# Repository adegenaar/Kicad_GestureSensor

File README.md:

# Kicad_GestureSensor
Small module utilizing the APDS-9990 for gesture sensing

The auto-generation of the KiCad exports was cribbed from:
* [nerdyscout](https://github.com/nerdyscout/kicad-exports)
* [INTI - CMNB](https://github.com/INTI-CMNB/KiBot)

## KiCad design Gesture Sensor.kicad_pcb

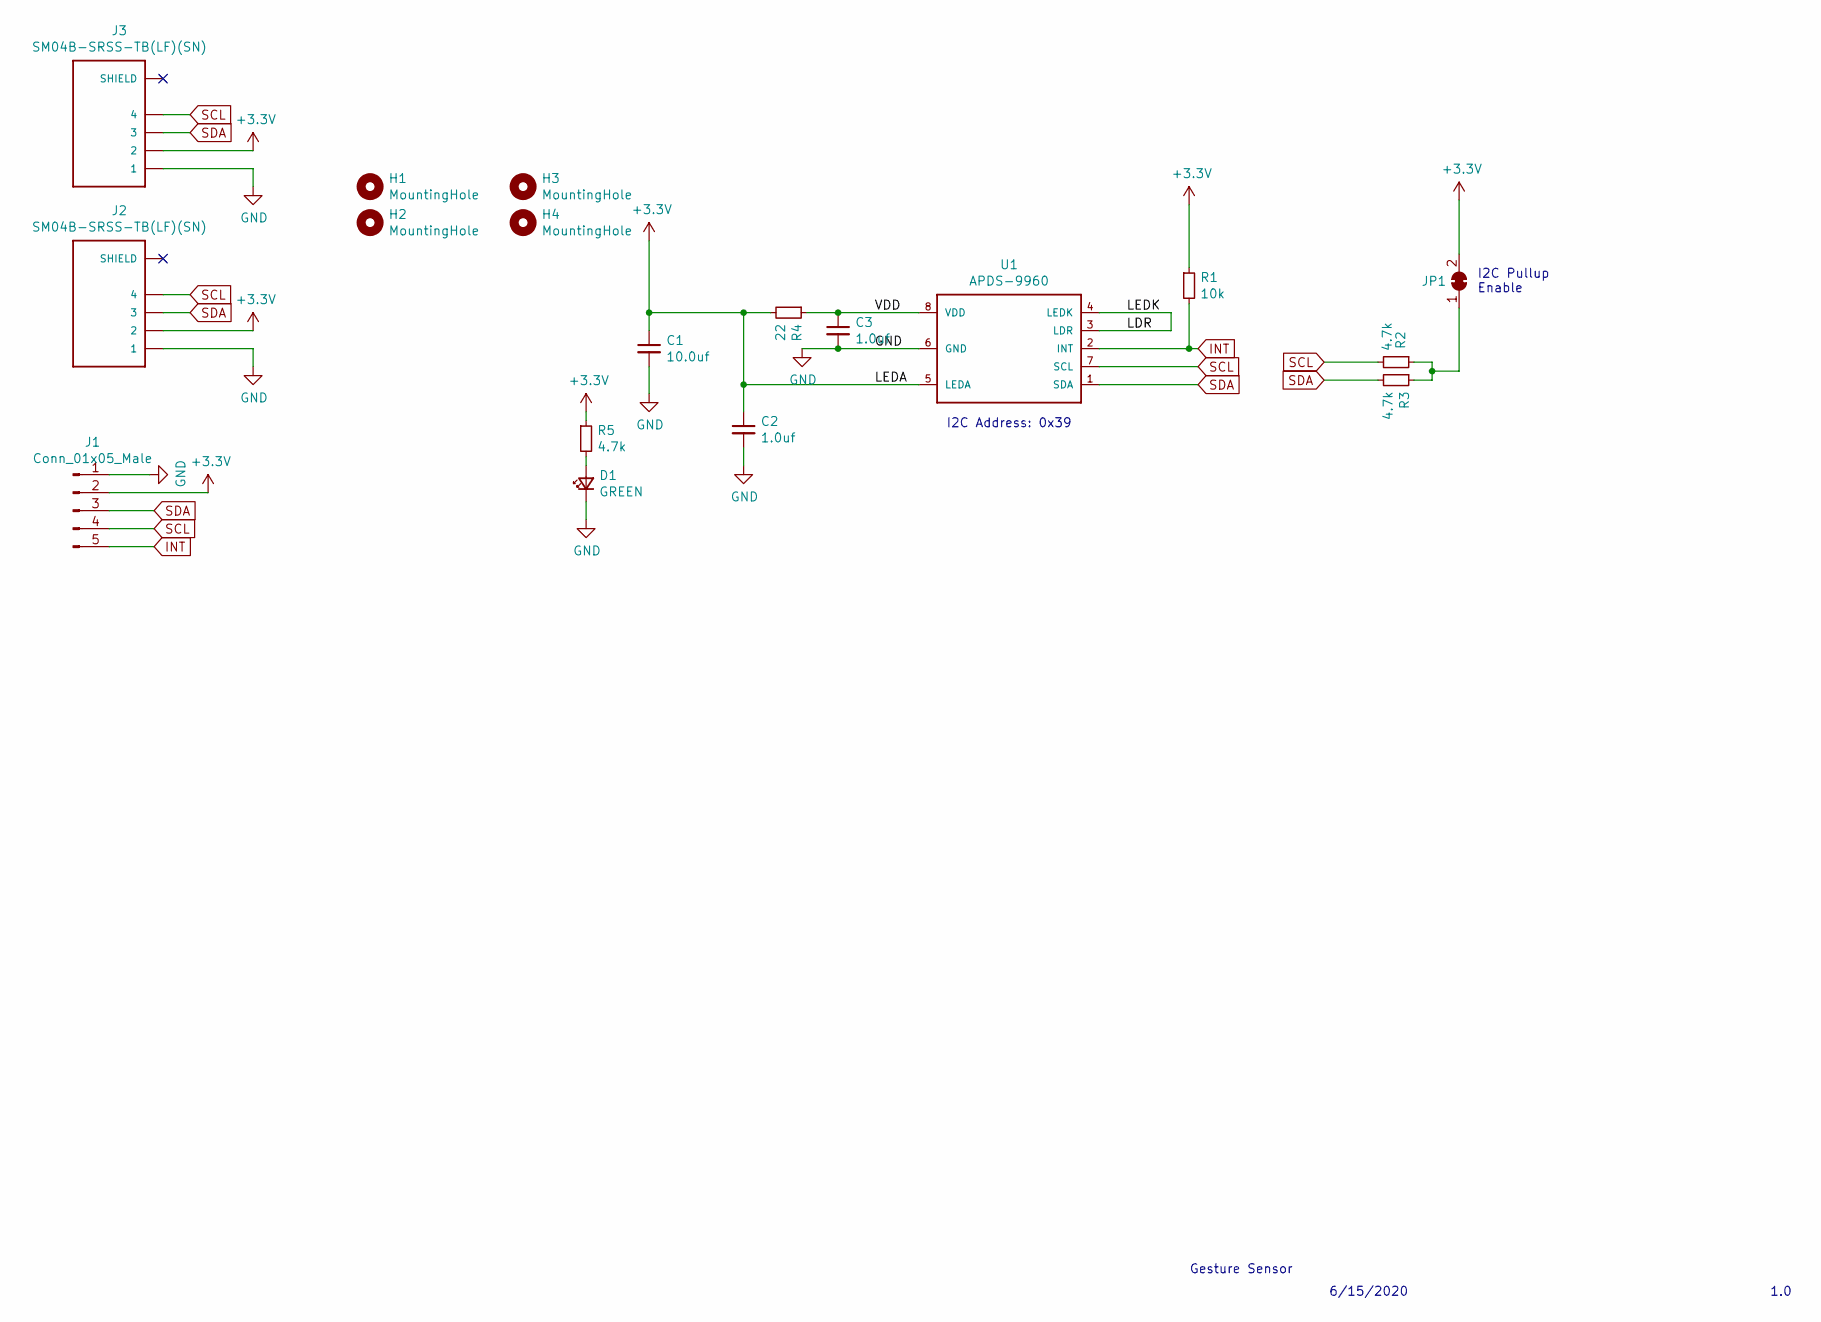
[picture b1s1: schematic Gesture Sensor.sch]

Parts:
C1: 10.0uf; C_0805_2012Metric_Pad1.15x1.40mm_HandSolder
C2, C3: 1.0uf; C_0805_2012Metric_Pad1.15x1.40mm_HandSolder
D1: GREEN; LED_0805_2012Metric
H1, H2, H3, H4: MountingHole; MountingHole_2.2mm_M2_ISO14580_Pad
J1: Conn_01x05_Male; PinHeader_1x05_P2.54mm_Vertical
J2, J3: SM04B-SRSS-TB(LF)(SN); JST_SM04B-SRSS-TB(LF)(SN)
JP1: SolderJumper_2_Bridged; SolderJumper-2_P1.3mm_Bridged_RoundedPad1.0x1.5mm
R1: 10k; R_0805_2012Metric_Pad1.15x1.40mm_HandSolder
R2, R3, R5: 4.7k; R_0805_2012Metric_Pad1.15x1.40mm_HandSolder
R4: 22; R_0805_2012Metric_Pad1.15x1.40mm_HandSolder
U1: APDS-9960

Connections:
+3V3: C1.1, C2.1, J1.2, J2.2, J3.2, JP1.2 (B), R1.1, R4.2, R5.1, U1.5 (LEDA)
/LDR: U1.3 (LDR), U1.4 (LEDK)
/VDD: C3.1, R4.1, U1.8 (VDD)
GND: C1.2, C2.2, C3.2, D1.1 (K), J1.1, J2.1, J3.1, U1.6 (GND)
INT: J1.5, R1.2, U1.2 (INT)
unnamed: D1.2 (A), R5.2
unnamed: J2.S1 (SHIELD), J2.S2 (SHIELD)
unnamed: J3.S1 (SHIELD), J3.S2 (SHIELD)
unnamed: JP1.1 (A), R2.1, R3.1
SCL: J1.4, J2.4, J3.4, R2.2, U1.7 (SCL)
SDA: J1.3, J2.3, J3.3, R3.2, U1.1 (SDA)

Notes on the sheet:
I2C Address: 0x39
I2C Pullup Enable
Gesture Sensor
6/15/2020
1.0

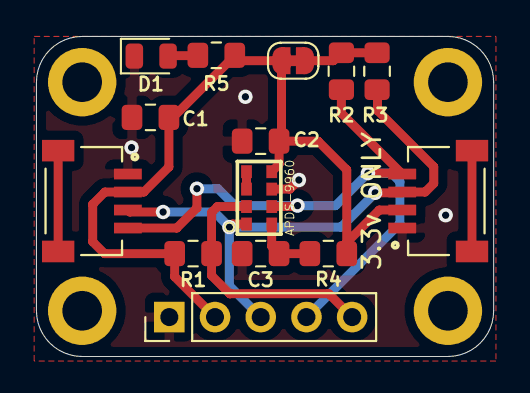
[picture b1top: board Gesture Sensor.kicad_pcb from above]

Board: 2 copper layers, 25.4 x 17.8 mm, 18 parts (0 on the bottom side), 11 nets.

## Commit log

2020-09-10 Add files via upload
    Initial version
2020-10-20 Create kicad.yml
    GitHub actions to generate the build artifacts from KiCad schematics
2020-10-20 Create docs.kiplot.yaml
    Config file for the actual generation of the artifacts
2020-10-20 Fixed schematic issue with Mosfet
2020-10-20 Create bom.kibot.yaml
    Configuration file to generate the BOM files from the schematic.
2020-10-20 Update kicad.yml
    Add BOM generation to the CI file
2020-10-20 Testing Actions
2020-10-20 Delete bom.kibot.yaml
    file was in the wrong place
2020-10-20 Delete docs.kiplot.yaml
    file was in the wrong place
2020-10-20 Generate ALL artifacts
2020-10-20 add workflow Dispatch to allow manual trigger
2020-10-20 Fixed typo
2020-10-20 added missing file
2020-10-20 moved file
2020-10-20 more updates
2020-10-20 remove xlsx from list
2020-10-20 remove another bom
2020-10-20 remove the last of the bom
2020-10-20 add commit
2020-10-20 Update README.md
    added links to the source for the KiCad exports
2020-10-20 test check in
2020-10-20 more testing
2020-10-20 testing
2020-10-20 update autogenerated files
